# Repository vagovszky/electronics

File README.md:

# electronics
HW stuff - Arduino, Nodemcu, etc.

## BTShield
Bluetooth shield for arduino - HC-06

## CLK_shield
RTC clock shield for Arduino - DS1307

## L298
2x DC motor driver/controller - L298

## LCD_I2C_shield
Shield for connecting arduino to I2C LCD controller

## MotorConnect
Shield for connecting arduino to L298 motor driver

## Relay
Module of 220V/10A relay

## USB_source
Power convertor from 12V battery to 5V USB

## Library
Set of eagle libraries

## Logic_Level_Bidirectional
Logic level convertor between 3.3V and 5V

## ESP8266_Thermometer
Wifi weather station with ESP8266

## Battery_Charger
Li-ion battery charger with OP Ampfs

## IoT_Module
IoT module with ESP8266

## Door_Sensor
Sensor of open door with ESP8266

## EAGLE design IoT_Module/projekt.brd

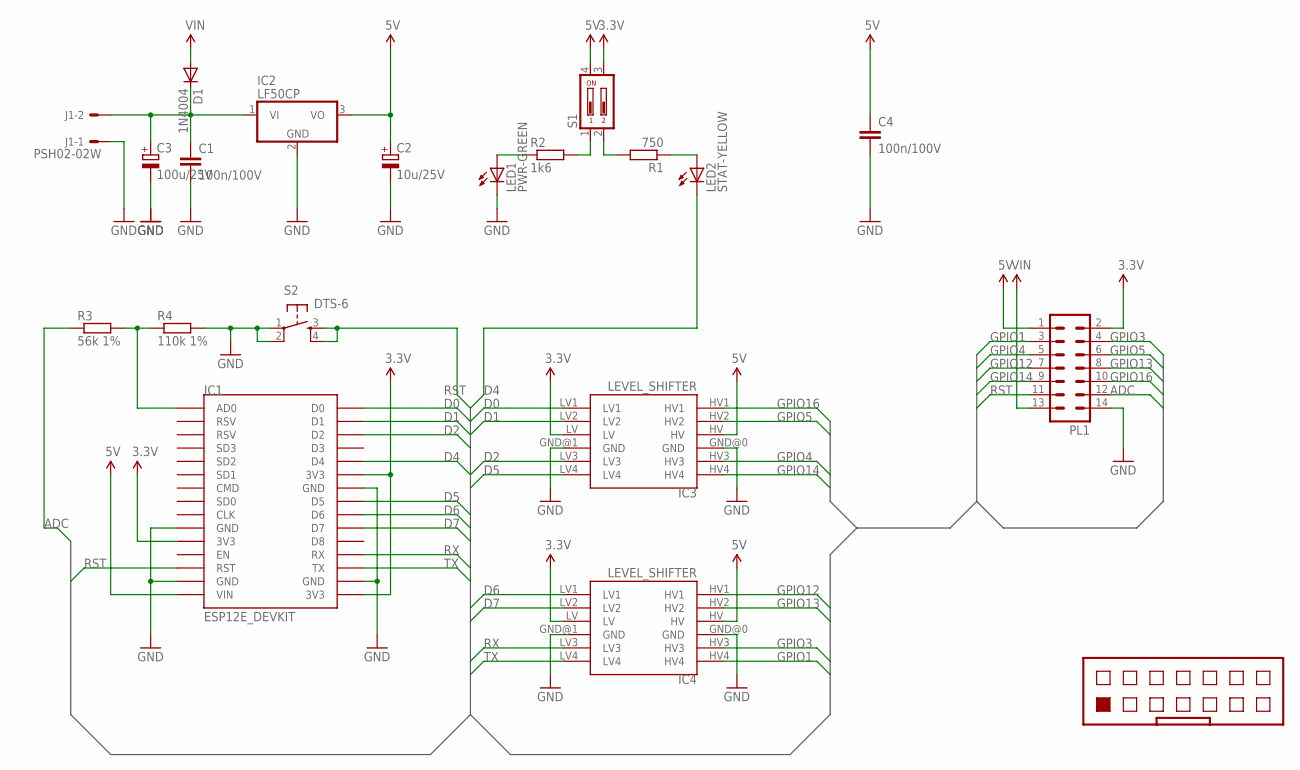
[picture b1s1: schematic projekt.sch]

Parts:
C1, C4: 100n/100V; C025-025X050
C2: 10u/25V; E3,5-8
C3: 100u/25V; E5-13
D1: 1N4004; DO41-10
IC1: ESP12E_DEVKIT
IC2: LF50CP; TO220H
IC3, IC4: LEVEL_SHIFTER
J1: PSH02-02W; 7395-02
LED1: PWR-GREEN; LED3MM
LED2: STAT-YELLOW; LED3MM
PL1: 14H
R1: 750; R1206
R2: 1k6; R1206
R3: 56k 1%; R1206
R4: 110k 1%; R1206
S1: DIP02YL
S2: DTS-6

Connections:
3.3V: IC1.3V3@0 (3V3), IC1.3V3@1 (3V3), IC1.3V3@2 (3V3), IC3.LV, IC4.LV, PL1.2, S1.3
5V: C2.+, C4.1, IC1.VIN, IC2.3 (VO), IC3.HV, IC4.HV, PL1.1, S1.4
ADC: PL1.12, R3.1
D0: IC1.D0, IC3.LV1
D1: IC1.D1, IC3.LV2
D2: IC1.D2, IC3.LV3
D4: IC1.D4, LED2.K (C)
D5: IC1.D5, IC3.LV4
D6: IC1.D6, IC4.LV1
D7: IC1.D7, IC4.LV2
GND: C1.2, C2.-, C3.-, C4.2, IC1.GND@0 (GND), IC1.GND@1 (GND), IC1.GND@2 (GND), IC1.GND@3 (GND), IC2.2 (GND), IC3.GND@0 (GND), IC3.GND@1 (GND), IC4.GND@0 (GND), IC4.GND@1 (GND), J1.1, LED1.K (C), PL1.14, R4.2, S2.1, S2.2
GPIO1: IC4.HV4, PL1.3
GPIO3: IC4.HV3, PL1.4
GPIO4: IC3.HV3, PL1.5
GPIO5: IC3.HV2, PL1.6
GPIO12: IC4.HV1, PL1.7
GPIO13: IC4.HV2, PL1.8
GPIO14: IC3.HV4, PL1.9
GPIO16: IC3.HV1, PL1.10
unnamed: IC1.AD0, R3.2, R4.1
unnamed: LED1.A, R2.1
unnamed: R2.2, S1.1
unnamed: R1.2, S1.2
unnamed: LED2.A, R1.1
unnamed: C1.1, C3.+, D1.C, IC2.1 (VI), J1.2
RST: IC1.RST, PL1.11, S2.3, S2.4
RX: IC1.RX, IC4.LV3
TX: IC1.TX, IC4.LV4
VIN: D1.A, PL1.13

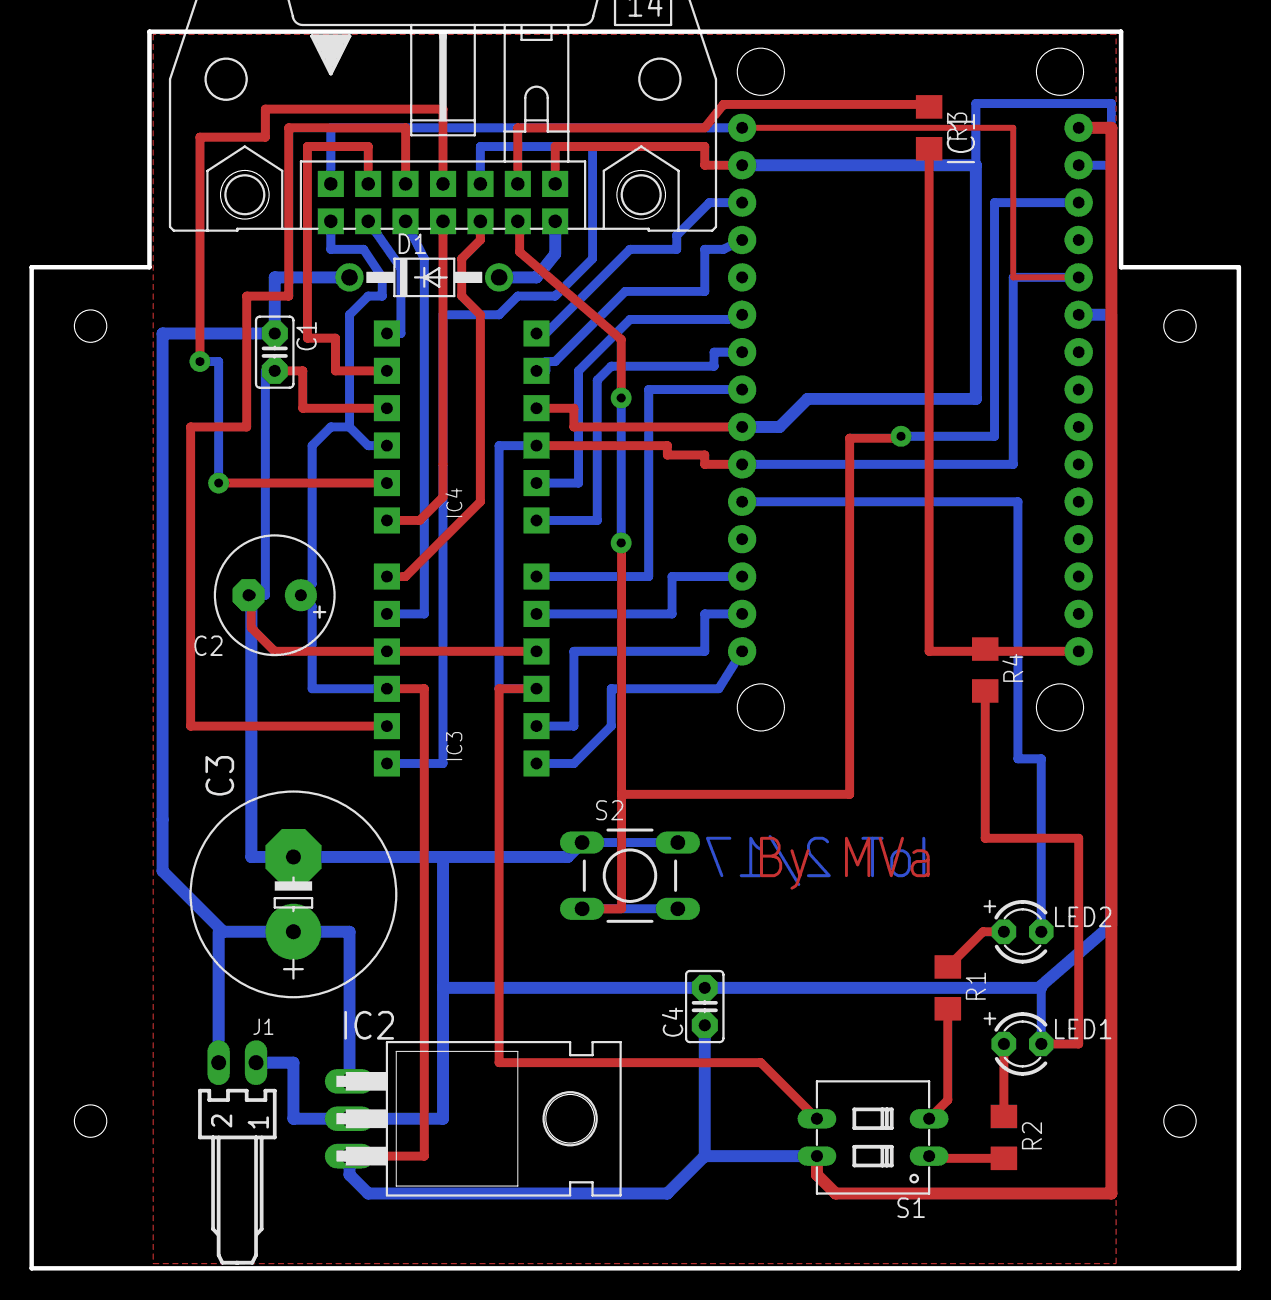
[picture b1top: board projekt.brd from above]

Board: 2 copper layers, 82.0 x 84.0 mm, 19 parts (0 on the bottom side), 29 nets.

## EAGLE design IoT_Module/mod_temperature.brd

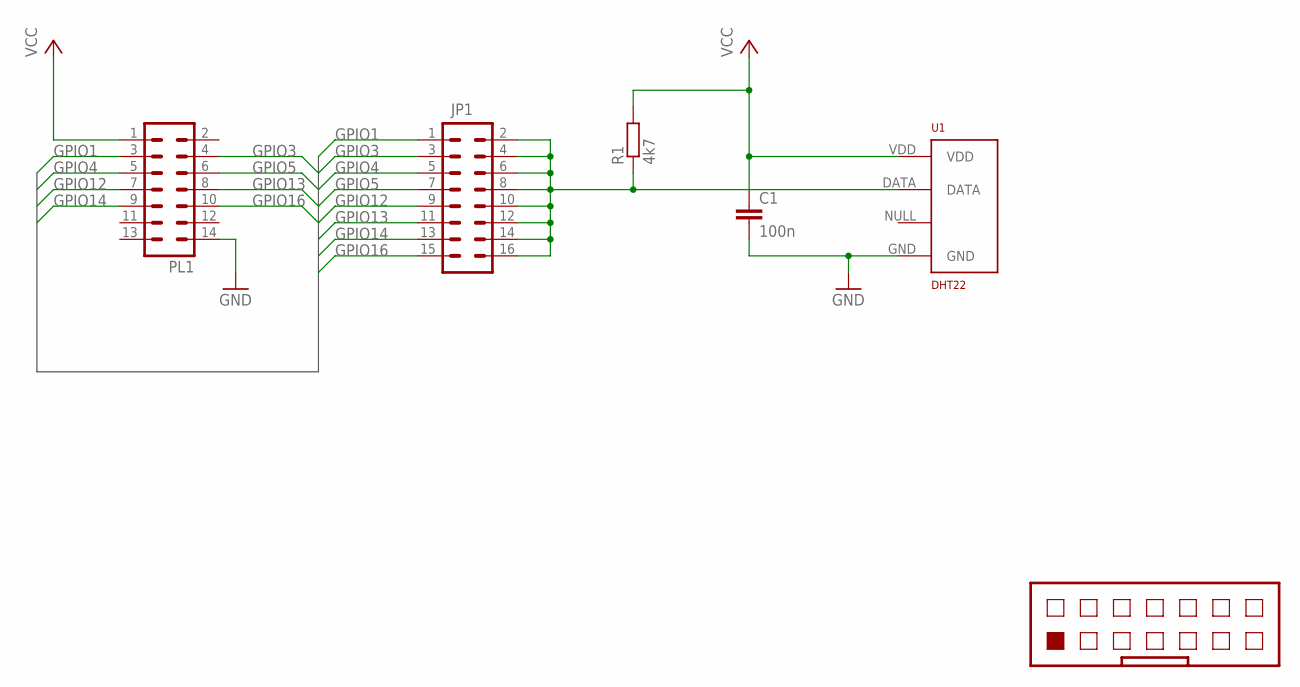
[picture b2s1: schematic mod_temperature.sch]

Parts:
C1: 100n; C025-025X050
JP1: M08X2; 2X8
PL1: 14V
R1: 4k7; 0207/10
U1: DHT22; RHT03_DHT-22/RA

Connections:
GND: C1.2, PL1.14, U1.GND
GPIO1: JP1.1, PL1.3
GPIO3: JP1.3, PL1.4
GPIO4: JP1.5, PL1.5
GPIO5: JP1.7, PL1.6
GPIO12: JP1.9, PL1.7
GPIO13: JP1.11, PL1.8
GPIO14: JP1.13, PL1.9
GPIO16: JP1.15, PL1.10
unnamed: JP1.2, JP1.4, JP1.6, JP1.8, JP1.10, JP1.12, JP1.14, JP1.16, R1.1, U1.DATA
VCC: C1.1, PL1.1, R1.2, U1.VDD

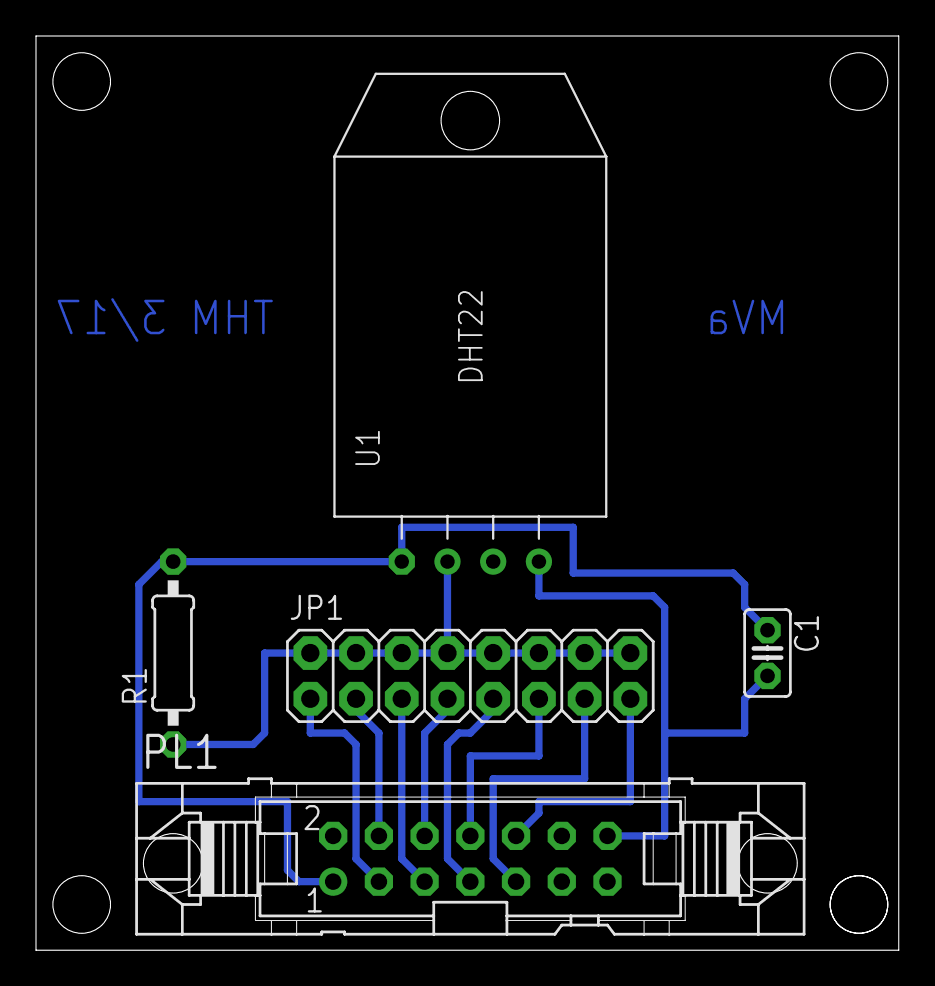
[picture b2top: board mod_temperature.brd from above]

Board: 2 copper layers, 47.9 x 50.8 mm, 5 parts (0 on the bottom side), 11 nets.

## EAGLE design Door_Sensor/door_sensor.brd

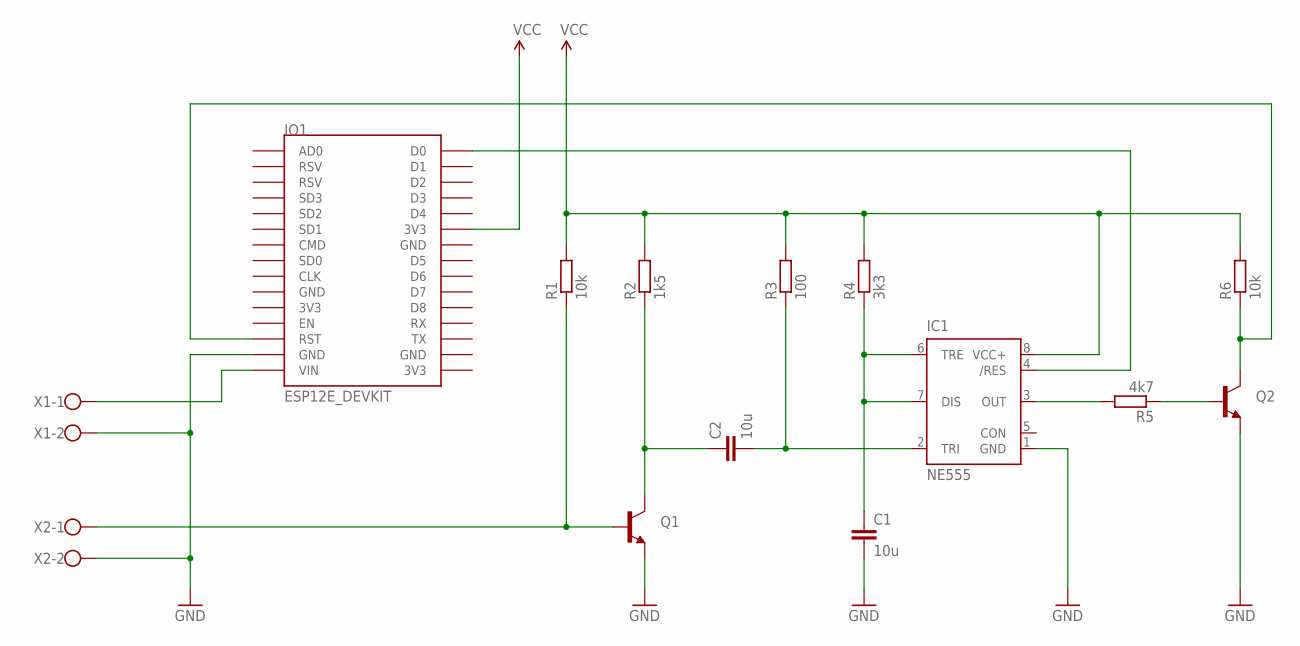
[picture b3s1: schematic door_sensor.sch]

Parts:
C1, C2: 10u; C025-025X050
IC1: NE555; DIL-08
IO1: ESP12E_DEVKIT
Q1, Q2: TRANSISTOR_NPN2N3904; TO-92
R1, R6: 10k; 0207/12
R2: 1k5; 0207/12
R3: 100; 0207/12
R4: 3k3; 0207/12
R5: 4k7; 0207/12
X1, X2: AK550/2

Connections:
GND: C1.2, IC1.1 (GND), IO1.GND@1 (GND), Q1.1 (E), Q2.1 (E), X1.2, X2.2
unnamed: C2.1, Q1.3 (C), R2.1
unnamed: Q1.2 (B), R1.1, X2.1
unnamed: C2.2, IC1.2 (TRI), R3.1
unnamed: IO1.VIN, X1.1
unnamed: IO1.RST, Q2.3 (C), R6.1
unnamed: Q2.2 (B), R5.1
unnamed: IC1.3 (OUT), R5.2
unnamed: C1.1, IC1.6 (TRE), IC1.7 (DIS), R4.1
unnamed: IC1.4 (/RES), IO1.D0
VCC: IC1.8 (VCC+), IO1.3V3@1 (3V3), R1.2, R2.2, R3.2, R4.2, R6.2

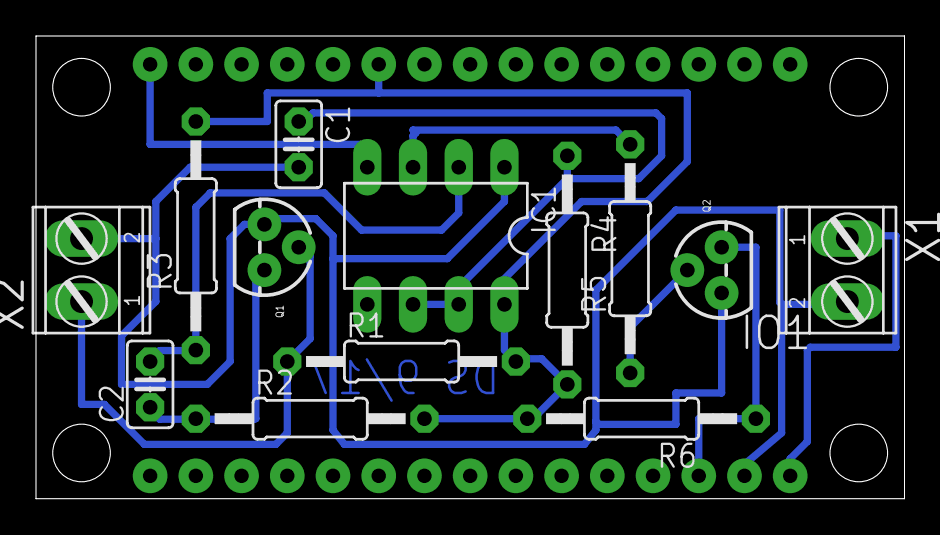
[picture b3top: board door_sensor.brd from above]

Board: 2 copper layers, 48.2 x 25.7 mm, 14 parts (0 on the bottom side), 11 nets.

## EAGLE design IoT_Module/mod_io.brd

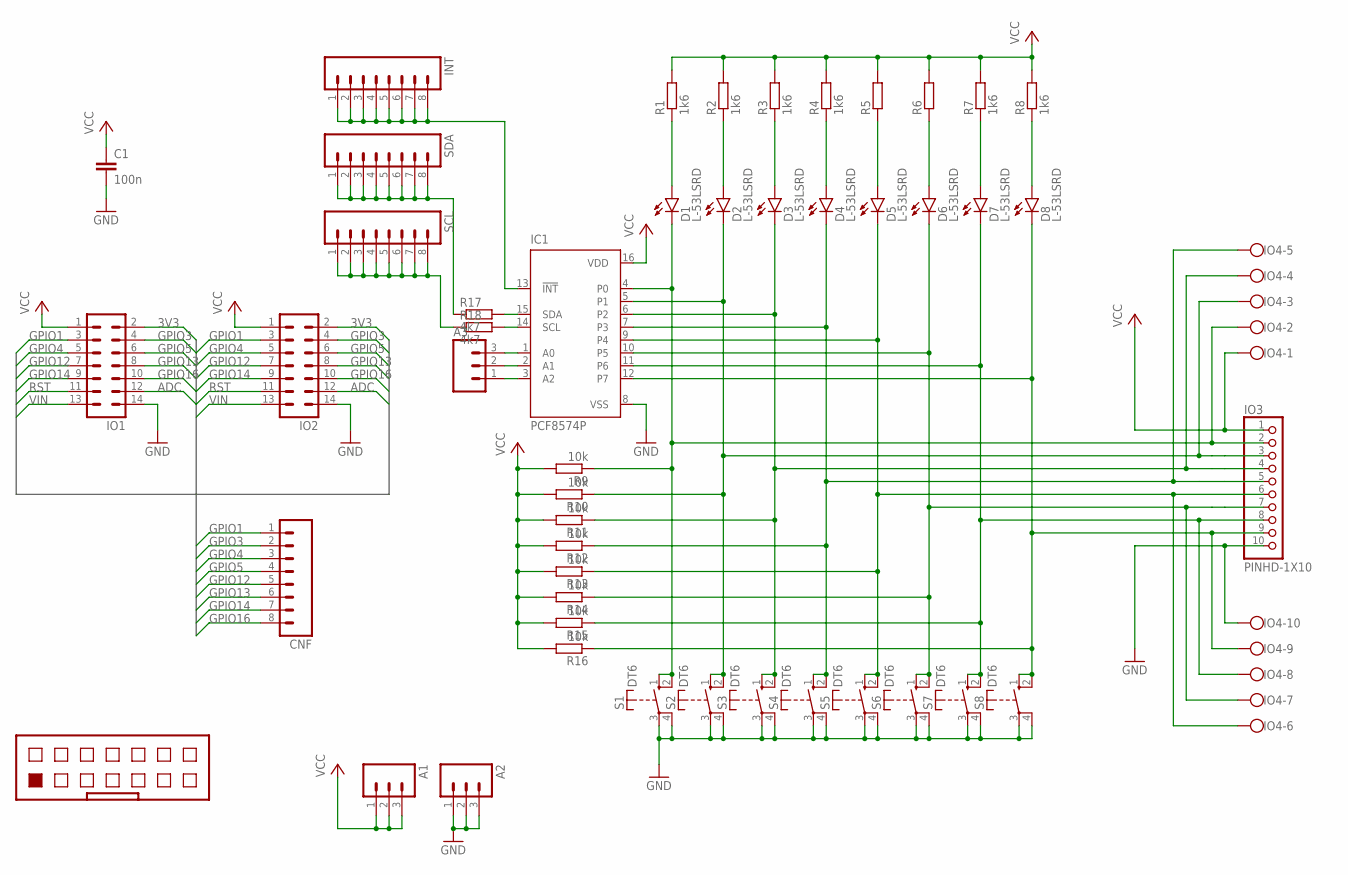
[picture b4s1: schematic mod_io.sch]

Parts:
A1, A2, A3: M03LONGPADS; 1X03_LONGPADS
C1: 100n; C050-025X075
CNF: M08LONGPADS; 1X08_LONGPADS
D1, D2, D3, D4, D5, D6, D7, D8: L-53LSRD; LED5MM
IC1: PCF8574P; DIL16
INT: M08LONGPADS; 1X08_LONGPADS
IO1, IO2: 14V
IO3: PINHD-1X10; 1X10-BIG
IO4: AK550/10
R1, R2, R3, R4, R7, R8: 1k6; 0207/10
R5, R6: R-EU_0207/10; 0207/10
R9, R10, R11, R12, R13, R14, R15, R16: 10k; 0207/10
R17, R18: 4k7; 0207/10
S1, S2, S3, S4, S5, S6, S7, S8: DT6
SCL: M08LONGPADS; 1X08_LONGPADS
SDA: M08LONGPADS; 1X08_LONGPADS

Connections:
3V3: IO1.2, IO2.2
ADC: IO1.12, IO2.12
GND: A2.1, A2.2, A2.3, C1.2, IC1.8 (VSS), IO1.14, IO2.14, IO3.10, IO4.10, S1.3, S1.4, S2.3, S2.4, S3.3, S3.4, S4.3, S4.4, S5.3, S5.4, S6.3, S6.4, S7.3, S7.4, S8.3, S8.4
GPIO1: CNF.1, IO1.3, IO2.3
GPIO3: CNF.2, IO1.4, IO2.4
GPIO4: CNF.3, IO1.5, IO2.5
GPIO5: CNF.4, IO1.6, IO2.6
GPIO12: CNF.5, IO1.7, IO2.7
GPIO13: CNF.6, IO1.8, IO2.8
GPIO14: CNF.7, IO1.9, IO2.9
GPIO16: CNF.8, IO1.10, IO2.10
unnamed: D5.K (C), IC1.9 (P4), IO3.6, IO4.6, R13.1, S5.1 (S), S5.2 (S)
unnamed: D6.K (C), IC1.10 (P5), IO3.7, IO4.7, R14.1, S6.1 (S), S6.2 (S)
unnamed: D1.K (C), IC1.4 (P0), IO3.2, IO4.2, R9.1, S1.1 (S), S1.2 (S)
unnamed: D2.K (C), IC1.5 (P1), IO3.3, IO4.3, R10.1, S2.1 (S), S2.2 (S)
unnamed: D3.K (C), IC1.6 (P2), IO3.4, IO4.4, R11.1, S3.1 (S), S3.2 (S)
unnamed: D4.K (C), IC1.7 (P3), IO3.5, IO4.5, R12.1, S4.1 (S), S4.2 (S)
unnamed: D7.K (C), IC1.11 (P6), IO3.8, IO4.8, R15.1, S7.1 (S), S7.2 (S)
unnamed: D8.K (C), IC1.12 (P7), IO3.9, IO4.9, R16.1, S8.1 (S), S8.2 (S)
unnamed: D6.A, R6.1
unnamed: D5.A, R5.1
unnamed: D7.A, R7.1
unnamed: D8.A, R8.1
unnamed: D1.A, R1.1
unnamed: D2.A, R2.1
unnamed: D3.A, R3.1
unnamed: D4.A, R4.1
unnamed: IC1.13 (!INT), INT.1, INT.2, INT.3, INT.4, INT.5, INT.6, INT.7, INT.8
unnamed: A3.3, IC1.1 (A0)
unnamed: A3.2, IC1.2 (A1)
unnamed: A3.1, IC1.3 (A2)
unnamed: IC1.15 (SDA), R17.2
unnamed: IC1.14 (SCL), R18.2
unnamed: R17.1, SDA.1, SDA.2, SDA.3, SDA.4, SDA.5, SDA.6, SDA.7, SDA.8
unnamed: R18.1, SCL.1, SCL.2, SCL.3, SCL.4, SCL.5, SCL.6, SCL.7, SCL.8
RST: IO1.11, IO2.11
VCC: A1.1, A1.2, A1.3, C1.1, IC1.16 (VDD), IO1.1, IO2.1, IO3.1, IO4.1, R1.2, R2.2, R3.2, R4.2, R5.2, R6.2, R7.2, R8.2, R9.2, R10.2, R11.2, R12.2, R13.2, R14.2, R15.2, R16.2
VIN: IO1.13, IO2.13

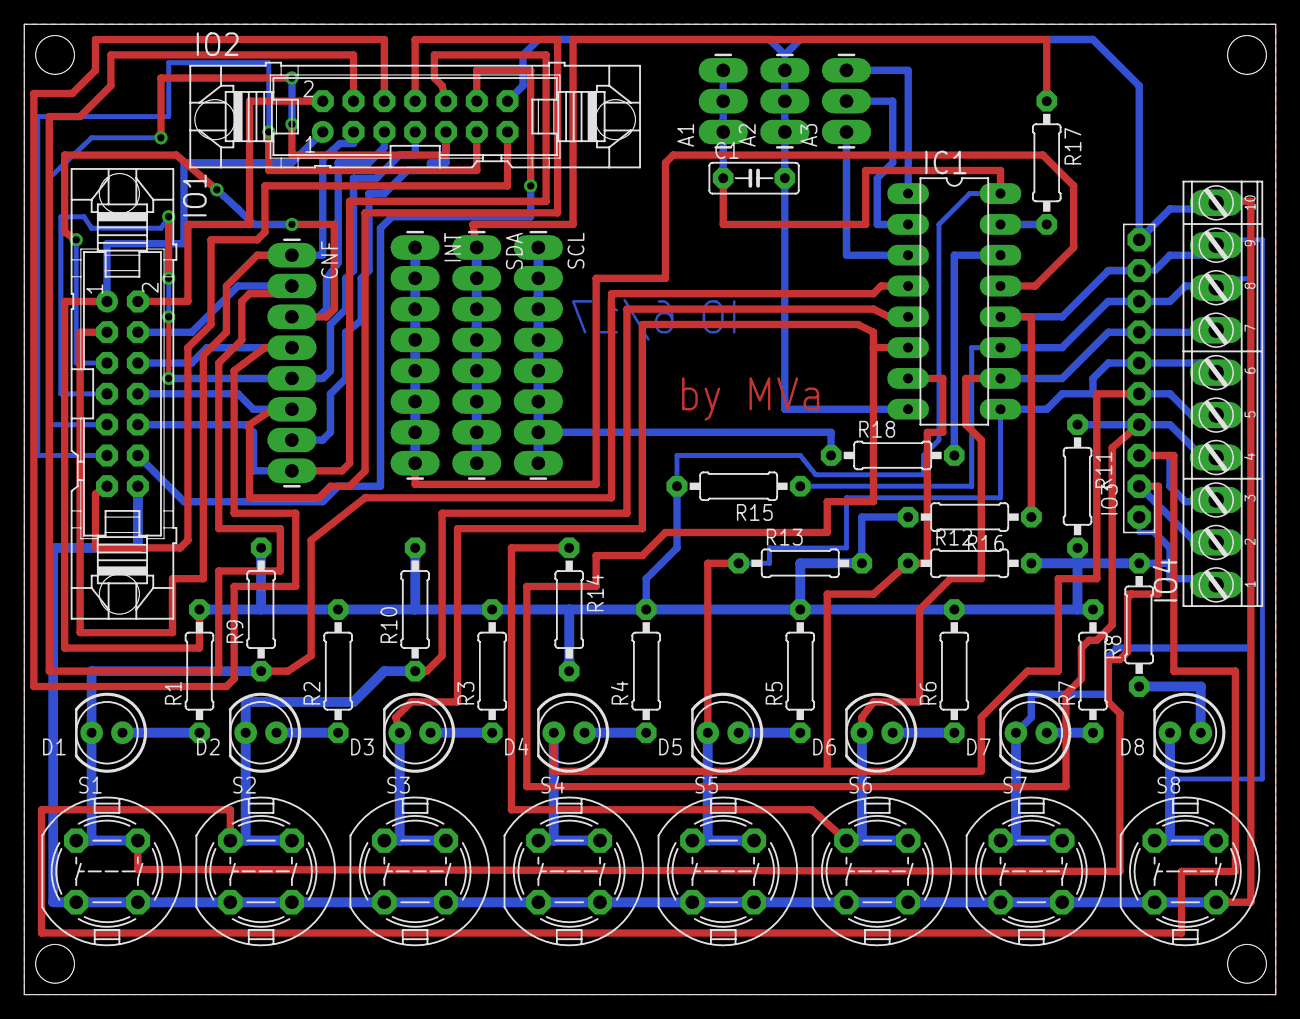
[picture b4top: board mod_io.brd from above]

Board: 2 copper layers, 103.2 x 80.0 mm, 47 parts (0 on the bottom side), 38 nets.

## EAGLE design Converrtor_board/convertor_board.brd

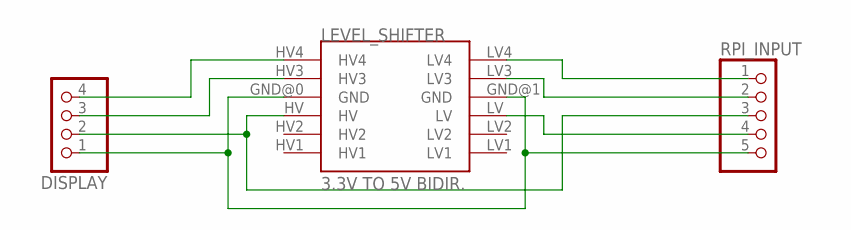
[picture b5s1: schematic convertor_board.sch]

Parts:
DISPLAY: PINHD-1X4; 1X04
LEVEL_SHIFTER: 3.3V TO 5V BIDIR.; LEVEL_SHIFTER
RPI_INPUT: PINHD-1X5; 1X05

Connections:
unnamed: DISPLAY.1, LEVEL_SHIFTER.GND@0 (GND), LEVEL_SHIFTER.GND@1 (GND), RPI_INPUT.5
unnamed: DISPLAY.3, LEVEL_SHIFTER.HV3
unnamed: DISPLAY.4, LEVEL_SHIFTER.HV4
unnamed: LEVEL_SHIFTER.LV, RPI_INPUT.4
unnamed: DISPLAY.2, LEVEL_SHIFTER.HV, RPI_INPUT.3
unnamed: LEVEL_SHIFTER.LV3, RPI_INPUT.2
unnamed: LEVEL_SHIFTER.LV4, RPI_INPUT.1

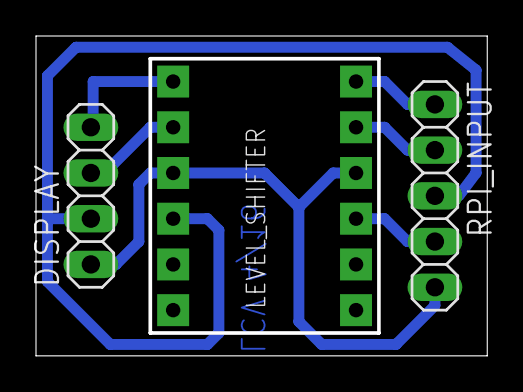
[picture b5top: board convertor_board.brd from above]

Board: 2 copper layers, 24.9 x 17.6 mm, 3 parts (0 on the bottom side), 7 nets.

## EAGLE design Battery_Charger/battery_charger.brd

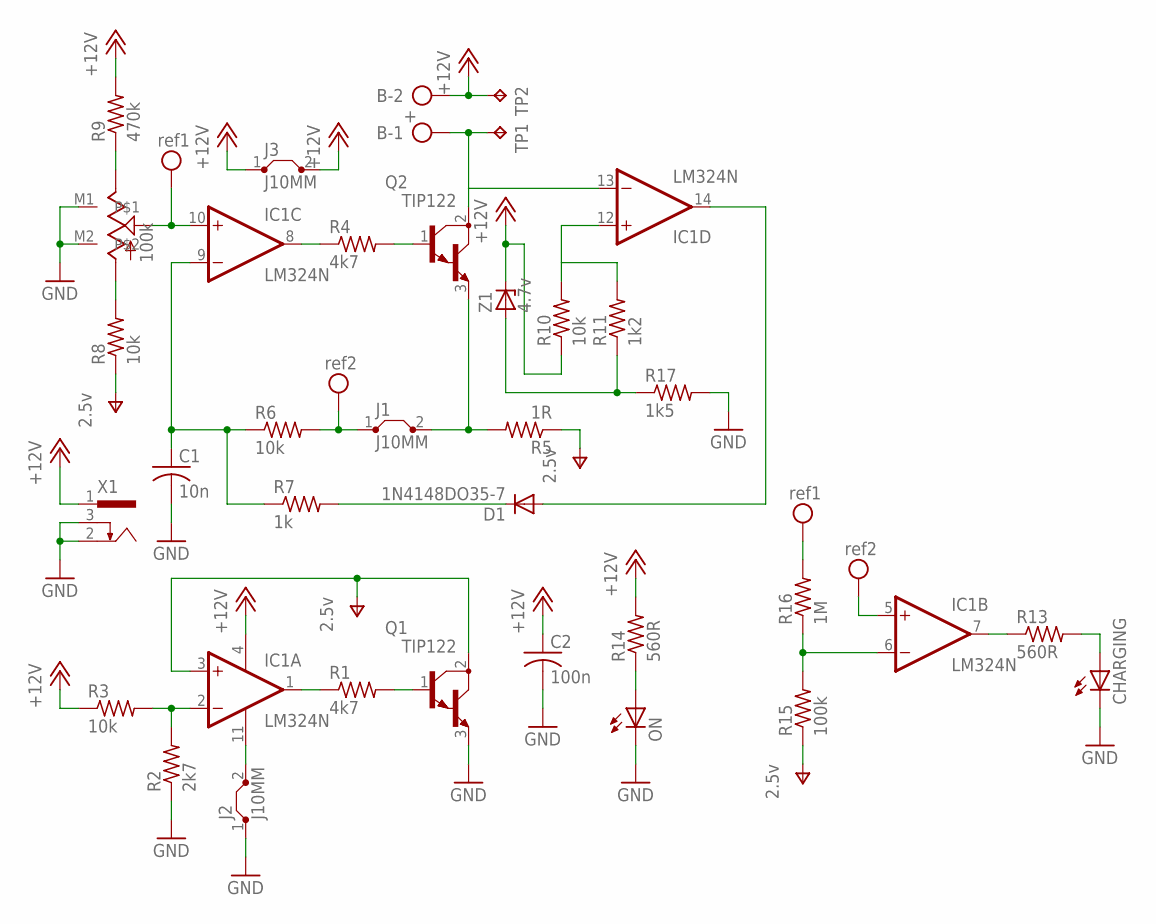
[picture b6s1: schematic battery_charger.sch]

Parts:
B: +; AK500/2
C1: 10n; C050-025X075
C2: 100n; C050-025X075
CHARGING: LED5MM
D1: 1N4148DO35-7; DO35-7
IC1: LM324N; DIL14
J1, J2, J3: J10MM; 10
ON: LED5MM
Q1, Q2: TIP122; TO220V
R1, R4: 4k7; 0207/7
R2: 2k7; 0207/7
R3, R6, R8, R10: 10k; 0207/7
R5: 1R; 0922/22
R7: 1k; 0207/7
R9: 470k; 0207/7
R11: 1k2; 0207/7
R12: 100k; EVUFXM
R13, R14: 560R; 0207/7
R15: 100k; 0207/7
R16: 1M; 0207/7
R17: 1k5; 0207/7
TP1, TP2: TPPAD1-13; P1-13
X1: 733980-62
Z1: 4.7v; DO34Z7

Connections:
+12V: B.2, C2.1, IC1.4 (V+), J3.1, J3.2, R3.1, R9.2, R10.1, R14.2, TP2.TP, X1.1, Z1.C
GND: C1.2, C2.2, CHARGING.K (C), J2.1, ON.K (C), Q1.3 (E), R2.1, R12.M1, R12.M2, R17.2, X1.2, X1.3
unnamed: IC1.1 (OUT), R1.1
unnamed: Q1.1 (B), R1.2
unnamed: IC1.8 (OUT), R4.1
unnamed: IC1.2 (-IN), R2.2, R3.2
unnamed: Q2.1 (B), R4.2
unnamed: ON.A, R14.1
unnamed: R11.1, R17.1, Z1.A
unnamed: B.1, IC1.13 (-IN), Q2.2 (C), TP1.TP
unnamed: C1.1, IC1.9 (-IN), R6.1, R7.1
unnamed: D1.C, R7.2
unnamed: D1.A, IC1.14 (OUT)
unnamed: R8.2, R12.1 (A)
unnamed: CHARGING.A, R13.2
unnamed: R9.1, R12.3 (E)
unnamed: IC1.7 (OUT), R13.1
unnamed: IC1.6 (-IN), R15.2, R16.1
unnamed: IC1.11 (V-), J2.2
unnamed: J1.2, Q2.3 (E), R5.2
unnamed: IC1.12 (+IN), R10.2, R11.2
V-: IC1.3 (+IN), Q1.2 (C), R5.1, R8.1, R15.1
VCC: IC1.10 (+IN), R12.2 (S), R16.2
VEE: IC1.5 (+IN), J1.1, R6.2

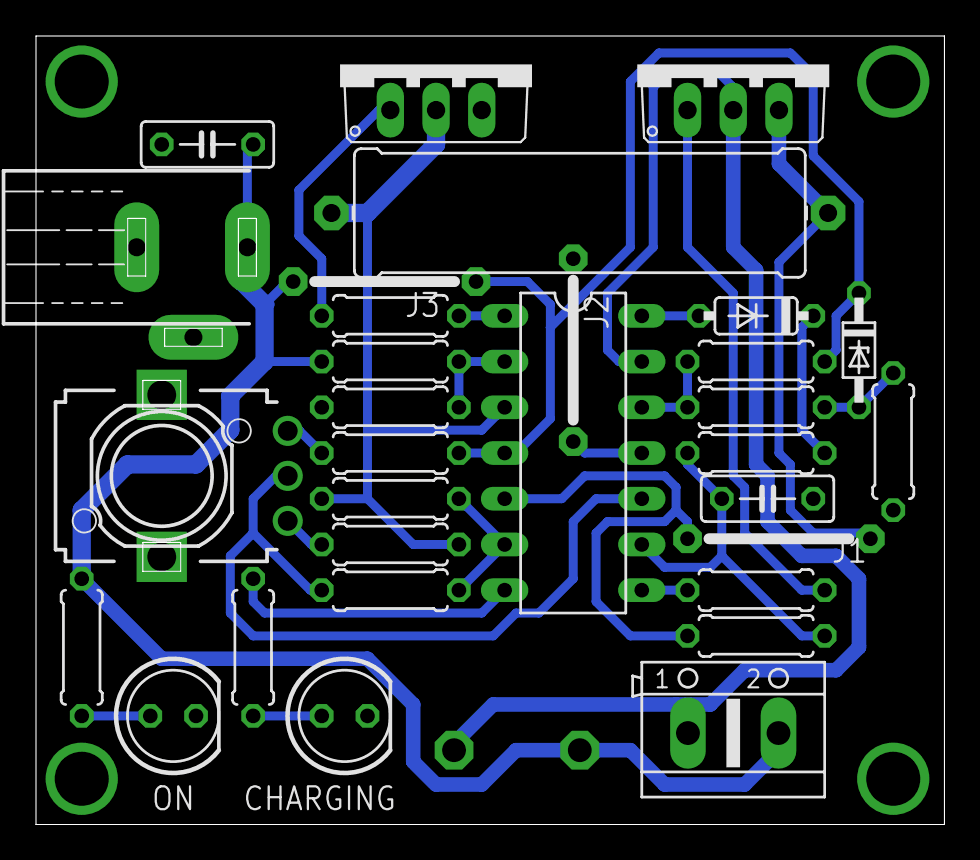
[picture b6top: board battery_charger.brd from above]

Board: 2 copper layers, 50.5 x 43.8 mm, 33 parts (0 on the bottom side), 24 nets.

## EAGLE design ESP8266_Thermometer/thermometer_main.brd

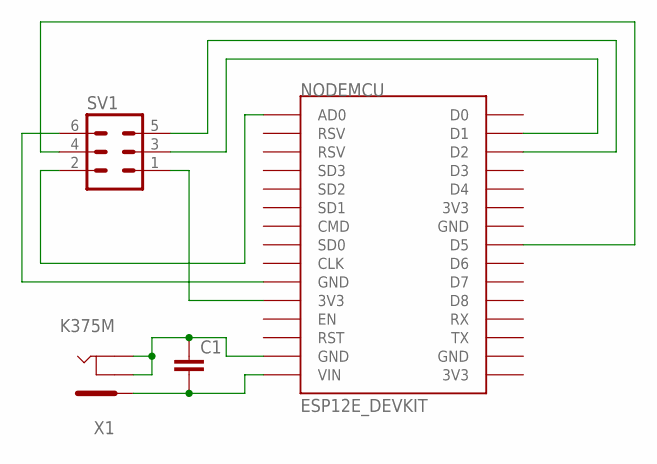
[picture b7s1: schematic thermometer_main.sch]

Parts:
C1: C-EU025-025X050; C025-025X050
NODEMCU: ESP12E_DEVKIT
SV1: ML6L
X1: K375M

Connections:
unnamed: C1.2, NODEMCU.VIN, X1.1
unnamed: NODEMCU.D2, SV1.5
unnamed: C1.1, NODEMCU.GND@1 (GND), X1.2, X1.3
unnamed: NODEMCU.AD0, SV1.2
unnamed: NODEMCU.3V3@0 (3V3), SV1.1
unnamed: NODEMCU.GND@0 (GND), SV1.6
unnamed: NODEMCU.D1, SV1.3
unnamed: NODEMCU.D5, SV1.4

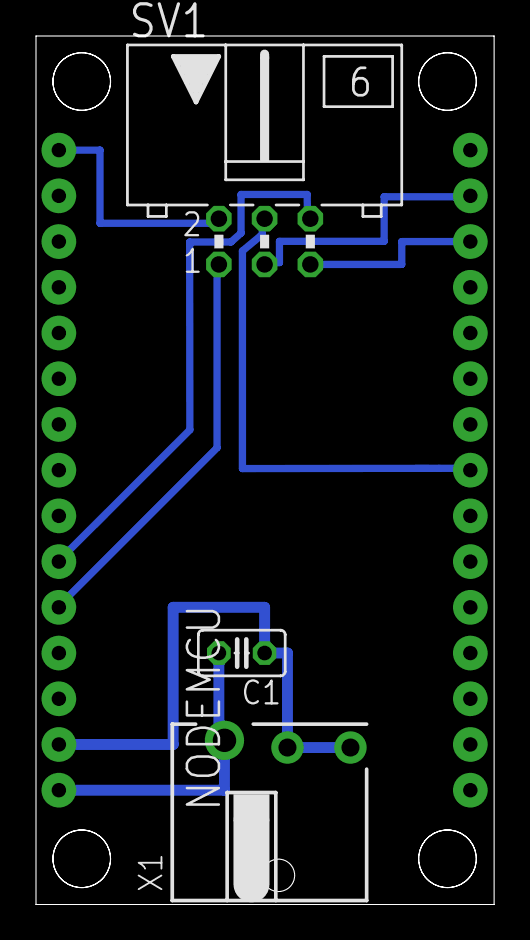
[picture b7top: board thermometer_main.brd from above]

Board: 2 copper layers, 25.5 x 48.2 mm, 4 parts (0 on the bottom side), 8 nets.

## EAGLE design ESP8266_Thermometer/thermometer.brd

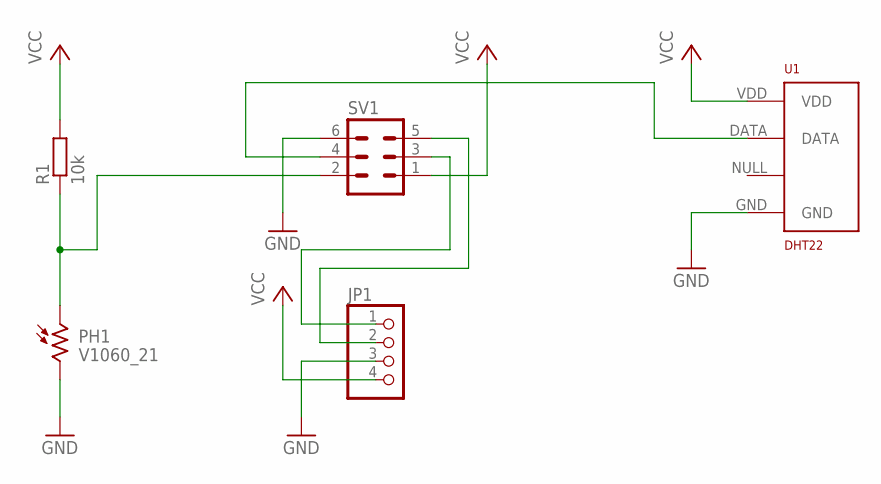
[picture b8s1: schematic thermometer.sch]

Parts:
JP1: PINHD-1X4; 1X04
PH1: V1060_21; TO-5_V10
R1: 10k; 0207/12
SV1: ML6
U1: DHT22; RHT03_DHT-22/RA

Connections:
GND: JP1.3, PH1.2, SV1.6, U1.GND
unnamed: PH1.1, R1.1, SV1.2
unnamed: JP1.1, SV1.3
unnamed: SV1.4, U1.DATA
unnamed: JP1.2, SV1.5
VCC: JP1.4, R1.2, SV1.1, U1.VDD

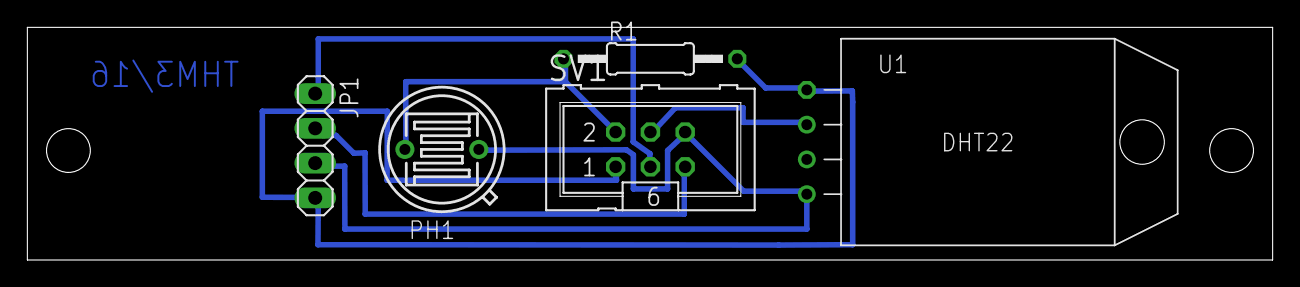
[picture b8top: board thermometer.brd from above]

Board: 2 copper layers, 91.0 x 17.0 mm, 5 parts (0 on the bottom side), 6 nets.

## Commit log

2015-12-20 Added eagle projects
2016-01-21 Add sparkfun Logic level converter.
2016-01-22 Data for board manufacturing
2016-03-14 Nodemcu thermometer
2016-03-15 Remove files
2016-03-15 Images for thermometer PCB manufacturing
2016-04-01 Added ESP8266_Thermometer to README
2016-05-11 Added Battery charger
2017-02-09 Added level_shifter.lbr
2017-03-12 Added IoT module
2017-04-12 Add lib dyi
2017-04-12 DHT22 Lib
2017-09-24 Added door sensor
2018-02-09 Added WiFi-devkits.lbr
2018-02-09 Updated DIY modules LBR
2018-02-09 Schema - robotdriver

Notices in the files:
parts and their libraries:
SparkFun-DiscreteSemi: Licensing: Creative Commons ShareAlike 4.0 International - https://creativecommons.org/licenses/by-sa/4.0
